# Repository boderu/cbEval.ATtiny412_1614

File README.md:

# cbEval.ATtiny412_1614

Evaluation-Board - basierend auf dem modularen Gehäuse von Camdenboss. ATtiny412 & ATtiny1614

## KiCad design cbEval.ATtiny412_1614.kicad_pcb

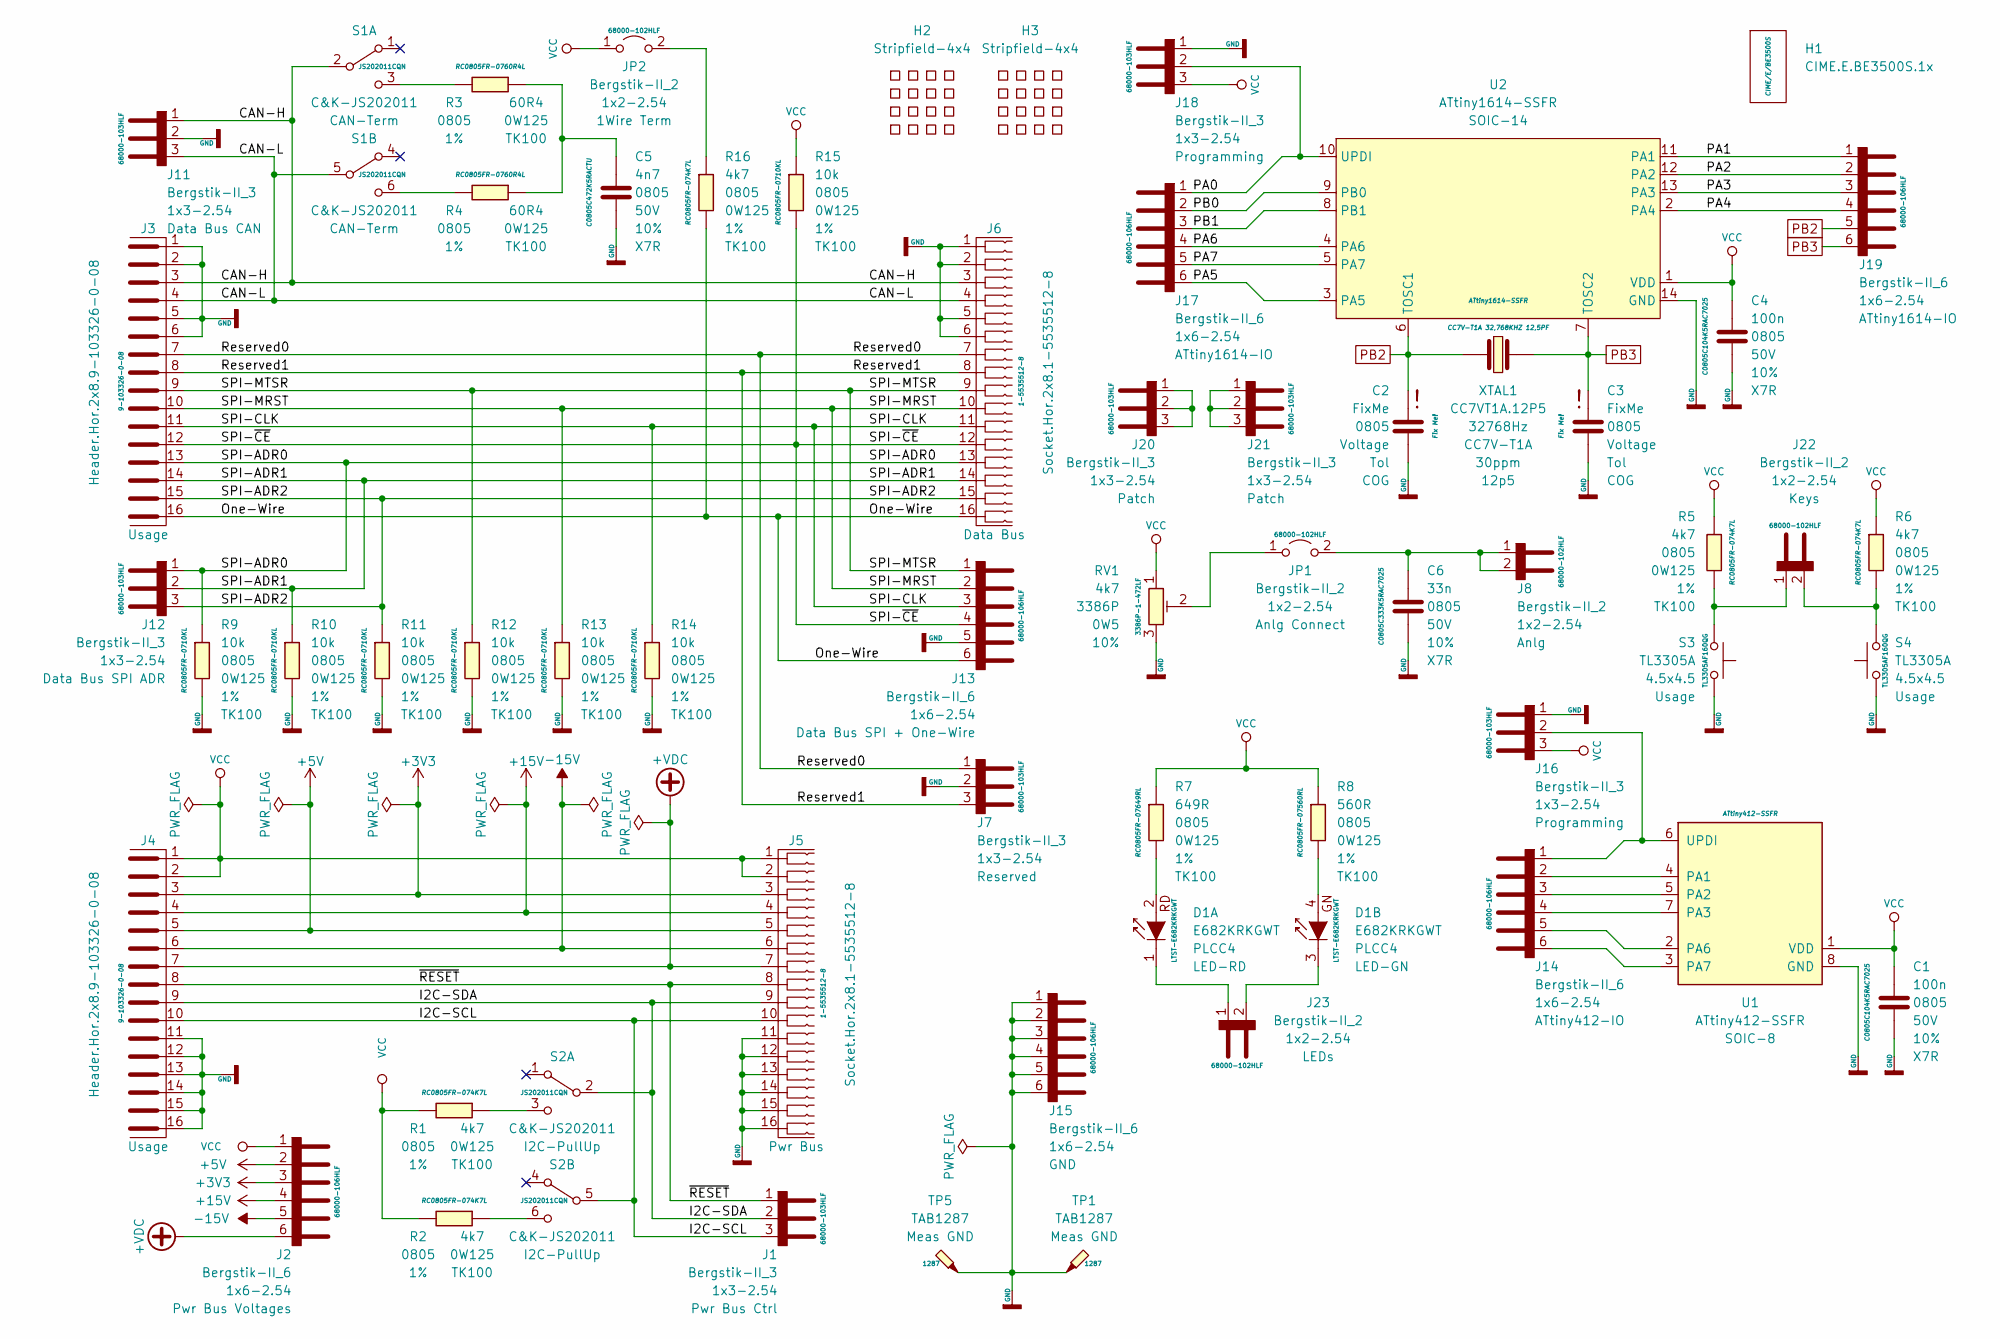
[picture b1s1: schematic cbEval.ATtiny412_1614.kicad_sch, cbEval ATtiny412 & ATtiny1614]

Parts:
C1, C4: 100n; C_0805_2012Metric; Voltage 50V; Tolerance 10%
C2, C3: FixMe; C_0805_2012Metric; Voltage Voltage; Tolerance Tol
C5: 4n7; C_0805_2012Metric; Voltage 50V; Tolerance 10%
C6: 33n; C_0805_2012Metric; Voltage 50V; Tolerance 10%
D1: E682KRKGWT; LED_Avago_PLCC4_3.2x2.8mm_CW
H1: CIME.E.BE3500S.1x; Camdenboss.CIME.E.BE3500S.1x
H2, H3: Stripfield-4x4
J1, J7, J11, J12, J16, J18, J20, J21: Bergstik-II_3; PinHeader_1x03_P2.54mm_Vertical
J2, J13, J14, J15, J17, J19: Bergstik-II_6; PinHeader_1x06_P2.54mm_Vertical
J3, J4: Header.Hor.2x8.9-103326-0-08; PinHeader_2x08_P2.54mm_Horizontal
J5, J6: Socket.Hor.2x8.1-5535512-8; Socket.Hor.2x5.6-5535512-4
J8, J22, J23: Bergstik-II_2; PinHeader_1x02_P2.54mm_Vertical
JP1, JP2: Bergstik-II_2; PinHeader_1x02_P2.54mm_Vertical
R1, R2, R5, R6, R16: 4k7; R_0805_2012Metric; Tolerance 1%
R3, R4: 60R4; R_0805_2012Metric; Tolerance 1%
R7: 649R; R_0805_2012Metric; Tolerance 1%
R8: 560R; R_0805_2012Metric; Tolerance 1%
R9, R10, R11, R12, R13, R14, R15: 10k; R_0805_2012Metric; Tolerance 1%
RV1: 4k7; Potentiometer_Bourns_3386P_Vertical; Tolerance 10%
S1, S2: C&K-JS202011; SW_CuK_JS202011CQN_DPDT_Straight
S3, S4: TL3305A; SW_SPST_TL3305A
TP1, TP5: TAB1287; TestPoint_Bridge_Pitch5.08mm_Drill1.3mm
U1: ATtiny412-SSFR; SOIC-8_3.9x4.9mm_P1.27mm
U2: ATtiny1614-SSFR; SOIC-14_3.9x8.7mm_P1.27mm
XTAL1: CC7VT1A.12P5; Crystal_SMD_MicroCrystal_CC7V-T1A-2Pin_3.2x1.5mm; Tolerance 30ppm

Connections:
+3V3: J2.3 (A3), J4.3, J5.3
+5V: J2.2 (A2), J4.5, J5.5
+15V: J2.4 (A4), J4.4, J5.4
+VDC: J2.6 (A6), J4.7, J5.7
-15V: J2.5 (A5), J4.6, J5.6
/CAN-H: J3.3, J6.3, J11.1 (A1), S1.2 (B)
/CAN-L: J3.4, J6.4, J11.3 (A3), S1.5 (B)
/I2C-SCL: J1.3 (A3), J4.10, J5.10, S2.5 (B)
/I2C-SDA: J1.2 (A2), J4.9, J5.9, S2.2 (B)
/One-Wire: J3.16, J6.16, J13.6 (A6), R16.2
/PA0: J17.1 (A1), J18.2 (A2), U2.10 (UPDI)
/PA1: J19.1 (A1), U2.11 (PA1)
/PA2: J19.2 (A2), U2.12 (PA2)
/PA3: J19.3 (A3), U2.13 (PA3)
/PA4: J19.4 (A4), U2.2 (PA4)
/PA5: J17.6 (A6), U2.3 (PA5)
/PA6: J17.4 (A4), U2.4 (PA6)
/PA7: J17.5 (A5), U2.5 (PA7)
/PB0: J17.2 (A2), U2.9 (PB0)
/PB1: J17.3 (A3), U2.8 (PB1)
/Reserved0: J3.7, J6.7, J7.1 (A1)
/Reserved1: J3.8, J6.8, J7.3 (A3)
/SPI-ADR0: J3.13, J6.13, J12.1 (A1), R9.1
/SPI-ADR1: J3.14, J6.14, J12.2 (A2), R10.1
/SPI-ADR2: J3.15, J6.15, J12.3 (A3), R11.1
/SPI-CLK: J3.11, J6.11, J13.3 (A3), R14.1
/SPI-MRST: J3.10, J6.10, J13.2 (A2), R13.1
/SPI-MTSR: J3.9, J6.9, J13.1 (A1), R12.1
/SPI-~CE: J3.12, J6.12, J13.4 (A4), R15.2
/~RESET: J1.1 (A1), J4.8, J5.8
GND: C1.2, C2.2, C3.2, C4.2, C5.2, C6.2, J3.1, J3.2, J3.5, J3.6, J4.11, J4.12, J4.13, J4.14, J4.15, J4.16, J5.11, J5.12, J5.13, J5.14, J5.15, J5.16, J6.1, J6.2, J6.5, J6.6, J7.2 (A2), J11.2 (A2), J13.5 (A5), J15.1 (A1), J15.2 (A2), J15.3 (A3), J15.4 (A4), J15.5 (A5), J15.6 (A6), J16.1 (A1), J18.1 (A1), R9.2, R10.2, R11.2, R12.2, R13.2, R14.2, RV1.3, S3.2, S4.2, TP1.1, TP5.1, U1.8 (GND), U2.14 (GND)
unnamed: C5.1, R3.1, R4.1
unnamed: C6.1, J8.1 (A1), J8.2 (A2), JP1.2 (B)
unnamed: D1.1 (Rd-C), J23.1 (A1)
unnamed: D1.2 (Rd-A), R7.2
unnamed: D1.3 (Gn-C), J23.2 (A2)
unnamed: D1.4 (Gn-A), R8.2
unnamed: J14.1 (A1), J16.2 (A2), U1.6 (UPDI)
unnamed: J14.2 (A2), U1.4 (PA1)
unnamed: J14.3 (A3), U1.5 (PA2)
unnamed: J14.4 (A4), U1.7 (PA3)
unnamed: J14.5 (A5), U1.2 (PA6)
unnamed: J14.6 (A6), U1.3 (PA7)
unnamed: J20.1 (A1), J20.2 (A2), J20.3 (A3)
unnamed: J21.1 (A1), J21.2 (A2), J21.3 (A3)
unnamed: J22.1 (A1), R5.2, S3.1
unnamed: J22.2 (A2), R6.2, S4.1
unnamed: JP1.1 (A), RV1.2
unnamed: JP2.2 (B), R16.1
unnamed: R1.1, S2.3 (C)
unnamed: R2.1, S2.6 (C)
unnamed: R3.2, S1.3 (C)
unnamed: R4.2, S1.6 (C)
PB2: C2.1, J19.5 (A5), U2.6 (TOSC1), XTAL1.1
PB3: C3.1, J19.6 (A6), U2.7 (TOSC2), XTAL1.2
VCC: C1.1, C4.1, J2.1 (A1), J4.1, J4.2, J5.1, J5.2, J16.3 (A3), J18.3 (A3), JP2.1 (A), R1.2, R2.2, R5.1, R6.1, R7.1, R8.1, R15.1, RV1.1, U1.1 (VDD), U2.1 (VDD)

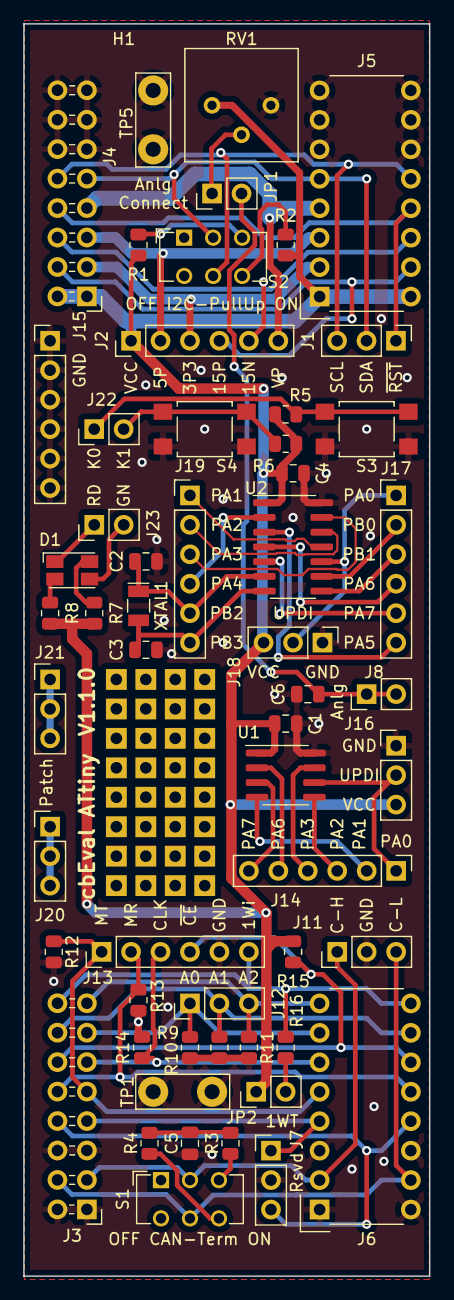
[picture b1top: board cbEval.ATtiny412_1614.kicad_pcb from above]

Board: 2 copper layers, 35.0 x 108.0 mm, 59 parts (0 on the bottom side), 56 nets.

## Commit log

2021-04-05 Schaltplan und grobe Platzierung fertig
2021-04-06 kleinere Änderungen
2021-04-10 BOM erstellt und kleinere Korrekturen
2021-04-10 Bus-Stecker ersetzt, Poti hinzugefügt
2021-04-11 1Wire-Terminierung hinzugefügt, BOM erneuert
2021-07-18 PowerBus-Belegung V1.1
2021-07-18 alle Verbindungen layoutet
2021-07-19 Design Rules an Beta-Layout angepasst
2021-12-27 Auf das Datenformat der Version 6 umgestellt
2021-12-30 fp-info-cache gelöscht
2022-01-23 Leiterplatte verkleinert, SilkScreen einiger Stecker verändert
2022-02-05 Kurzschluss entfernt, Vorwiderstand für grüne LEDs auf 560 verringert
2022-02-22 Ignore-Liste erweitert
2023-11-08 Update auf KiCAD V7
